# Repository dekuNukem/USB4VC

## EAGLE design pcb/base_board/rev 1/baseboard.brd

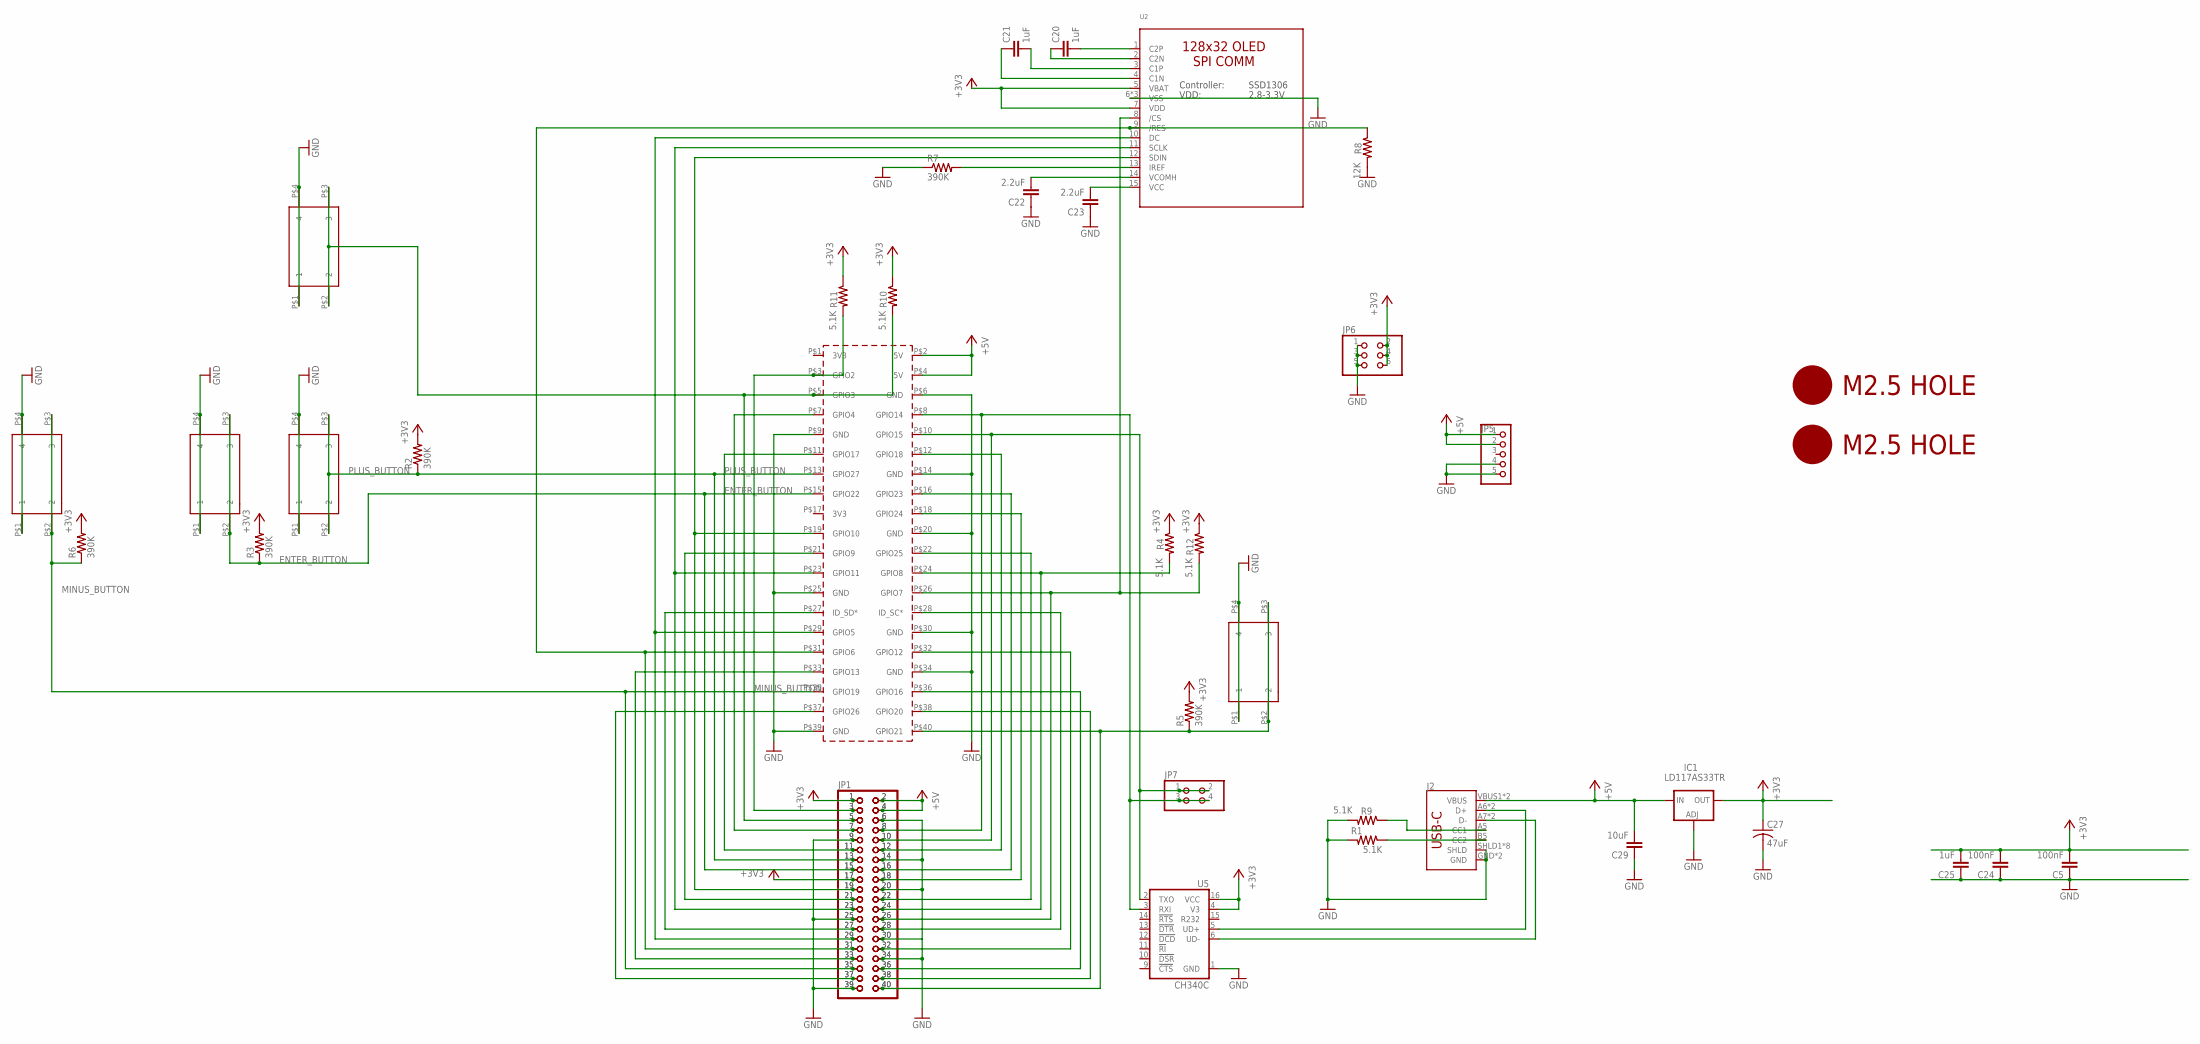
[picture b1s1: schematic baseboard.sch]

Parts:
C5, C24: 100nF; 0805
C20, C21, C25: 1uF; 0805
C22, C23: 2.2uF; 0805
C27: 47uF; C1210
C29: 10uF; 0805
IC1: LD117AS33TR; SOT223
J2: USB_C16PIN; USB-C-16P
JP1, JP2: PINHD-2X20-BIG; 2X20-BIG
JP5: PINHD-1X5; 1X05
JP6: PINHD-2X3; 2X03
JP7: PINHD-2X2; 2X02
PCB1: RPI3NO-CONNECTORS; RPI3-NO-CONNECTORS
R1, R4, R9, R10, R11, R12: 5.1K; 0805
R2, R3, R5, R6, R7: 390K; 0805
R8: 12K; 0805
SW1, SW2, SW3, SW4, SW20: 324_SW; 342_SWICH_FOOT
U2: LUL_DISP_OLED_UG-2864HSWEG01; LUL_UG-2864HSWEG01_1.3_WRAPAROUND
U5: CH340C; SO016
U$2, U$3: M2.5HOLE

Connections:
+3V3: C5.2, C24.2, C25.2, C27.1, IC1.4 (OUT), JP1.1, JP1.17, JP2.1, JP2.17, JP6.2, JP6.4, JP6.6, R2.2, R3.2, R4.1, R5.2, R6.2, R10.1, R11.1, R12.1, U2.5 (VBAT), U2.7 (VDD), U5.4 (V3), U5.16 (VCC); also elsewhere on the board
+5V: C29.2, IC1.3 (IN), J2.VBUS1 (VBUS), J2.VBUS2 (VBUS), JP1.2, JP1.4, JP2.2, JP2.4, JP5.1, JP5.2, JP5.3, PCB1.P$2 (5V), PCB1.P$4 (5V)
ENTER_BUTTON: JP1.15, JP2.15, PCB1.P$15 (GPIO22), R3.1, SW20.P$2 (2), SW20.P$3 (3)
GND: C5.1, C22.1, C23.1, C24.1, C25.1, C27.2, C29.1, IC1.1 (ADJ), J2.GND, J2.GND2 (GND), J2.SHLD1 (SHLD), J2.SHLD2 (SHLD), J2.SHLD3 (SHLD), J2.SHLD4 (SHLD), J2.SHLD5 (SHLD), J2.SHLD6 (SHLD), J2.SHLD7 (SHLD), J2.SHLD8 (SHLD), JP1.6, JP1.9, JP1.14, JP1.20, JP1.25, JP1.30, JP1.34, JP1.39, JP2.6, JP2.9, JP2.14, JP2.20, JP2.25, JP2.30, JP2.34, JP2.39, JP5.4, JP5.5, JP6.1, JP6.3, JP6.5, PCB1.P$6 (GND), PCB1.P$9 (GND), PCB1.P$14 (GND), PCB1.P$20 (GND), PCB1.P$25 (GND), PCB1.P$30 (GND), PCB1.P$34 (GND), PCB1.P$39 (GND), R1.2, R7.1, R8.2, R9.2, SW1.P$1 (1), SW1.P$4 (4), SW2.P$1 (1), SW2.P$4 (4), SW3.P$1 (1), SW3.P$4 (4), SW4.P$1 (1), SW4.P$4 (4), SW20.P$1 (1), SW20.P$4 (4), U2.6 (VSS), U2.16 (VSS), U2.17 (VSS), U5.1 (GND); also elsewhere on the board
MINUS_BUTTON: JP1.35, JP2.35, PCB1.P$35 (GPIO19), R6.1, SW4.P$2 (2), SW4.P$3 (3)
unnamed: J2.A6 (D+), J2.B6 (D+), U5.5 (UD+)
unnamed: J2.A5 (CC1), R9.1
unnamed: J2.A7 (D-), J2.B7 (D-), U5.6 (UD-)
unnamed: JP1.3, JP2.3, PCB1.P$3 (GPIO2), R11.2
unnamed: JP1.5, JP2.5, PCB1.P$5 (GPIO3), R10.2, SW2.P$2 (2), SW2.P$3 (3)
unnamed: J2.B5 (CC2), R1.1
unnamed: JP1.7, JP2.7, PCB1.P$7 (GPIO4)
unnamed: JP1.11, JP2.11, PCB1.P$11 (GPIO17)
unnamed: JP1.19, JP2.19, PCB1.P$19 (GPIO10), U2.12 (SDIN)
unnamed: JP1.21, JP2.21, PCB1.P$21 (GPIO9)
unnamed: JP1.23, JP2.23, PCB1.P$23 (GPIO11), U2.11 (SCLK)
unnamed: JP1.27, JP2.27, PCB1.P$27 (ID_SD*)
unnamed: JP1.29, JP2.29, PCB1.P$29 (GPIO5), U2.10 (DC)
unnamed: JP1.33, JP2.33, PCB1.P$33 (GPIO13)
unnamed: JP1.37, JP2.37, PCB1.P$37 (GPIO26)
unnamed: JP1.12, JP2.12, PCB1.P$12 (GPIO18)
unnamed: JP1.16, JP2.16, PCB1.P$16 (GPIO23)
unnamed: JP1.18, JP2.18, PCB1.P$18 (GPIO24)
unnamed: JP1.22, JP2.22, PCB1.P$22 (GPIO25)
unnamed: JP1.24, JP2.24, PCB1.P$24 (GPIO8), R4.2
unnamed: JP1.26, JP2.26, PCB1.P$26 (GPIO7), R12.2, U2.8 (/CS)
unnamed: JP1.28, JP2.28, PCB1.P$28 (ID_SC*)
unnamed: JP1.32, JP2.32, PCB1.P$32 (GPIO12)
unnamed: JP1.36, JP2.36, PCB1.P$36 (GPIO16)
unnamed: JP1.38, JP2.38, PCB1.P$38 (GPIO20)
unnamed: JP1.40, JP2.40, PCB1.P$40 (GPIO21), R5.1, SW3.P$2 (2), SW3.P$3 (3)
unnamed: C20.2, U2.1 (C2P)
unnamed: C20.1, U2.2 (C2N)
unnamed: C21.2, U2.3 (C1P)
unnamed: C21.1, U2.4 (C1N)
unnamed: R7.2, U2.13 (IREF)
unnamed: C22.2, U2.14 (VCOMH)
unnamed: C23.2, U2.15 (VCC)
unnamed: JP1.31, JP2.31, PCB1.P$31 (GPIO6), R8.1, U2.9 (/RES)
PLUS_BUTTON: JP1.13, JP2.13, PCB1.P$13 (GPIO27), R2.1, SW1.P$2 (2), SW1.P$3 (3)
RPI_RX: JP1.10, JP2.10, JP7.1, JP7.2, PCB1.P$10 (GPIO15), U5.2 (TXO)
RPI_TX: JP1.8, JP2.8, JP7.3, JP7.4, PCB1.P$8 (GPIO14), U5.3 (RXI)

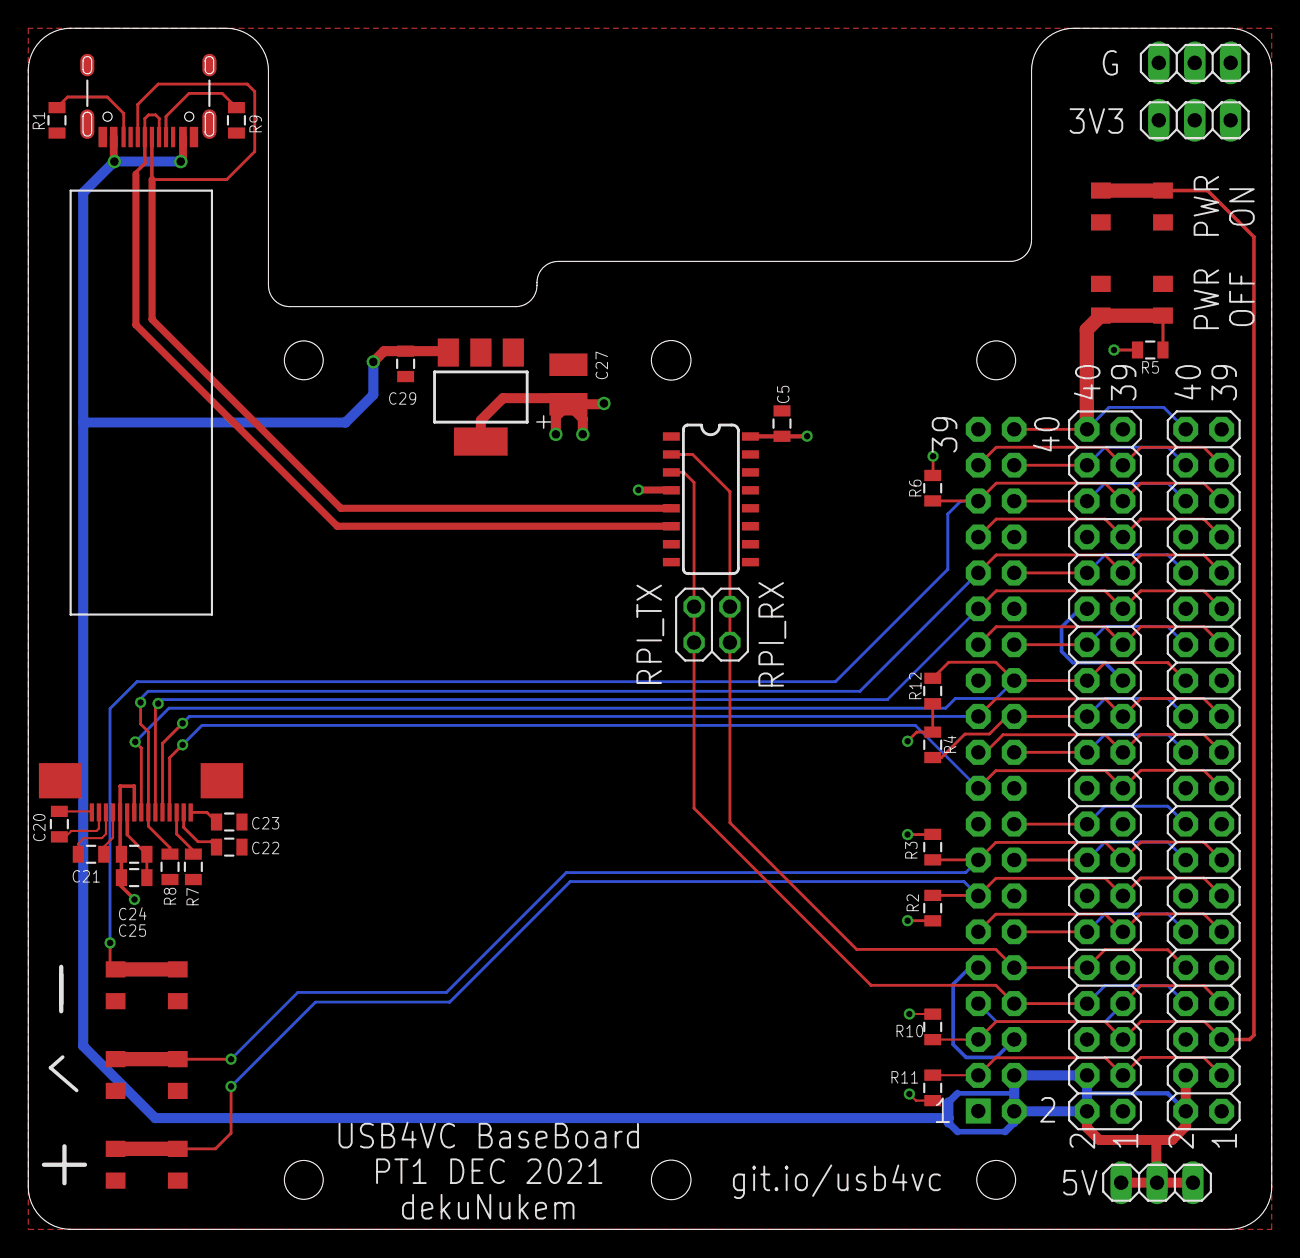
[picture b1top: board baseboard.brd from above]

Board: 2 copper layers, 88.0 x 85.0 mm, 39 parts (0 on the bottom side), 42 nets.

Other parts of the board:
JP3, JP4: 1X03

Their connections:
+3V3: JP3.1, JP3.2, JP3.3; also elsewhere on the board
GND: JP4.1, JP4.2, JP4.3; also elsewhere on the board

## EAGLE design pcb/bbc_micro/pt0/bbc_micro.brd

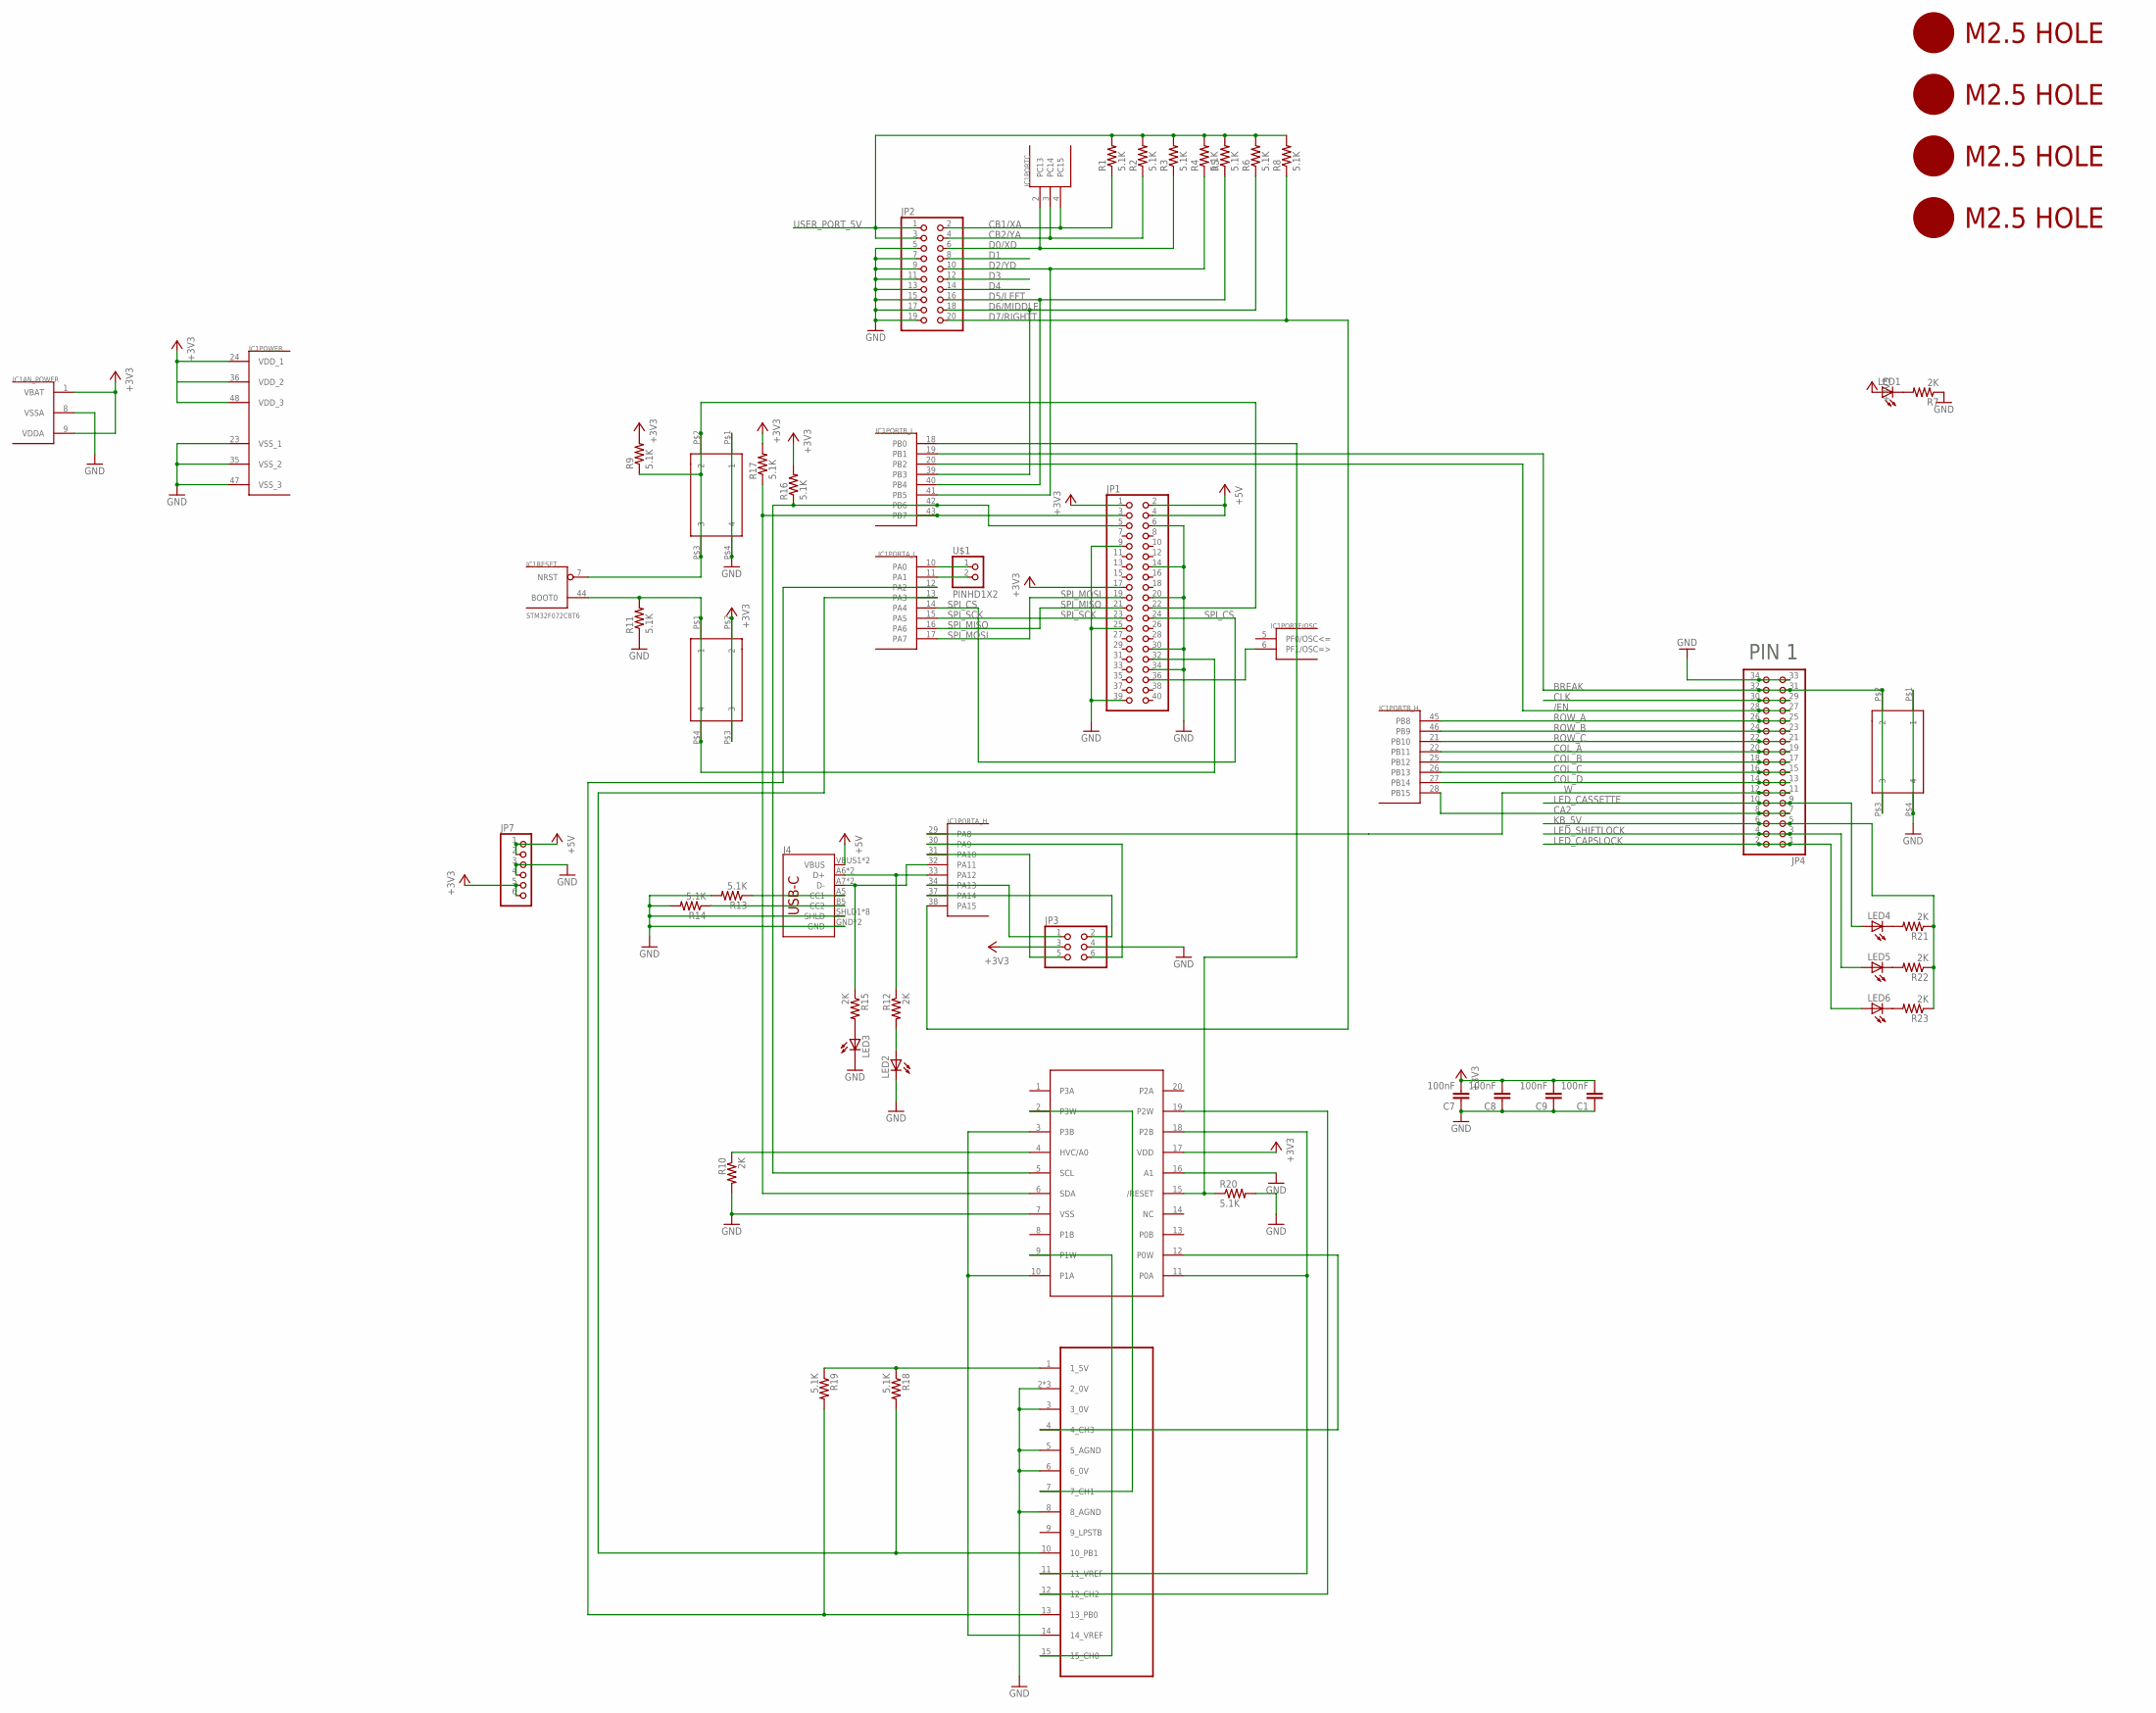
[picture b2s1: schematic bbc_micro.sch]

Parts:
C1, C7, C8, C9: 100nF; 0805@1
IC1: STM32F072C8T6; TQFP48
J4: USB_C16PIN; USB-C-16P
JP1: PINHD-2X20-BIG; 2X20-BIG
JP2: PINHD-2X10/90; 2X10/90
JP3: PINHD-2X3; 2X03
JP4: PINHD-2X17/90; 2X17/90
JP7: PINHD-1X6CB; 1X06-CLEANBIG
LED1, LED2, LED3, LED4, LED5, LED6: LEDCHIP-LED0805; CHIP-LED0805
R1, R2, R3, R4, R5, R6, R8, R9, R11, R13, R14, R16, R17, R18, R19, R20: 5.1K; 0805
R7, R10, R12, R15, R21, R22, R23: 2K; 0805
SW1, SW2, SW3: 324_SW; 342_SWICH_FOOT
U$1: PINHD1X2; 1X02
U$2, U$3, U$6, U$7: M2.5HOLE
U$5: MCP4451; TSSOP20
U$9: BBC_15P; DA15

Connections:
+3V3: C1.2, C7.2, C8.2, C9.2, IC1.1 (VBAT), IC1.9 (VDDA), IC1.24 (VDD_1), IC1.36 (VDD_2), IC1.48 (VDD_3), JP1.1, JP1.17, JP3.3, JP7.5, JP7.6, LED1.A, R9.2, R16.2, R17.2, SW2.P$2 (2), SW2.P$3 (3), U$5.17 (VDD)
+5V: J4.VBUS1 (VBUS), J4.VBUS2 (VBUS), JP1.2, JP1.4, JP7.1, JP7.2
/EN: IC1.20 (PB2), JP4.27, JP4.28
BREAK: IC1.19 (PB1), JP4.31, JP4.32, SW3.P$2 (2), SW3.P$3 (3)
CA2: IC1.28 (PB15), JP4.7, JP4.8
CB1/XA: IC1.4 (PC15), JP2.2, R1.1
CB2/YA: IC1.3 (PC14), JP2.4, R2.1
CLK: JP4.29, JP4.30
COL_A: IC1.22 (PB11), JP4.19, JP4.20
COL_B: IC1.25 (PB12), JP4.17, JP4.18
COL_C: IC1.26 (PB13), JP4.15, JP4.16
COL_D: IC1.27 (PB14), JP4.13, JP4.14
D0/XD: IC1.2 (PC13), JP2.6, R3.1
D1: JP2.8
D2/YD: IC1.41 (PB5), JP2.10, R4.1
D3: JP2.12
D4: JP2.14
D5/LEFT: IC1.40 (PB4), JP2.16, R5.1
D6/MIDDLE: IC1.39 (PB3), JP2.18, R6.1
D7/RIGHTT: IC1.38 (PA15), JP2.20, R8.1
GND: C1.1, C7.1, C8.1, C9.1, IC1.8 (VSSA), IC1.23 (VSS_1), IC1.35 (VSS_2), IC1.47 (VSS_3), J4.GND, J4.GND2 (GND), J4.SHLD1 (SHLD), J4.SHLD2 (SHLD), J4.SHLD3 (SHLD), J4.SHLD4 (SHLD), J4.SHLD5 (SHLD), J4.SHLD6 (SHLD), J4.SHLD7 (SHLD), J4.SHLD8 (SHLD), JP1.6, JP1.9, JP1.14, JP1.20, JP1.25, JP1.30, JP1.34, JP1.39, JP2.5, JP2.7, JP2.9, JP2.11, JP2.13, JP2.15, JP2.17, JP2.19, JP3.4, JP4.33, JP4.34, JP7.3, JP7.4, LED2.C, LED3.C, R7.1, R10.2, R11.1, R13.2, R14.2, R20.2, SW1.P$1 (1), SW1.P$4 (4), SW3.P$1 (1), SW3.P$4 (4), U$5.7 (VSS), U$5.16 (A1), U$9.2 (2_0V), U$9.3 (3_0V), U$9.5 (5_AGND), U$9.6 (6_0V), U$9.8 (8_AGND), U$9.G1 (2_0V), U$9.G2 (2_0V)
KB_5V: JP4.5, JP4.6, R21.1, R22.1, R23.1
LED_CAPSLOCK: JP4.1, JP4.2, LED6.A
LED_CASSETTE: JP4.9, JP4.10, LED4.A
LED_SHIFTLOCK: JP4.3, JP4.4, LED5.A
unnamed: J4.A5 (CC1), R13.1
unnamed: LED2.A, R12.2
unnamed: LED4.C, R21.2
unnamed: R10.1, U$5.4 (HVC/A0)
unnamed: U$5.2 (P3W), U$9.7 (7_CH1)
unnamed: U$5.9 (P1W), U$9.15 (15_CH0)
unnamed: J4.B5 (CC2), R14.1
unnamed: IC1.33 (PA12), J4.A6 (D+), J4.B6 (D+), R12.1
unnamed: IC1.32 (PA11), J4.A7 (D-), J4.B7 (D-), R15.1
unnamed: U$5.19 (P2W), U$9.12 (12_CH2)
unnamed: U$5.12 (P0W), U$9.4 (4_CH3)
unnamed: IC1.31 (PA10), JP3.5
unnamed: IC1.7 (NRST), JP1.22, R9.1, SW1.P$2 (2), SW1.P$3 (3)
unnamed: IC1.30 (PA9), JP3.6
unnamed: IC1.34 (PA13), JP3.1
unnamed: IC1.37 (PA14), JP3.2
unnamed: U$5.3 (P3B), U$5.10 (P1A), U$9.14 (14_VREF)
unnamed: IC1.44 (BOOT0), JP1.32, R11.2, SW2.P$1 (1), SW2.P$4 (4)
unnamed: U$5.11 (P0A), U$5.18 (P2B), U$9.11 (11_VREF)
unnamed: R18.1, R19.1, U$9.1 (1_5V)
unnamed: IC1.13 (PA3), R18.2, U$9.10 (10_PB1)
unnamed: IC1.42 (PB6), JP1.5, R16.1, U$5.5 (SCL)
unnamed: IC1.43 (PB7), JP1.3, R17.1, U$5.6 (SDA)
unnamed: IC1.10 (PA0), U$1.1
unnamed: IC1.18 (PB0), R20.1, U$5.15 (/RESET)
unnamed: LED5.C, R22.2
unnamed: LED6.C, R23.2
unnamed: LED3.A, R15.2
unnamed: LED1.C, R7.2
unnamed: IC1.12 (PA2), R19.2, U$9.13 (13_PB0)
unnamed: IC1.11 (PA1), U$1.2
unnamed: IC1.6 (PF1/OSC=>), JP1.36
ROW_A: IC1.45 (PB8), JP4.25, JP4.26
ROW_B: IC1.46 (PB9), JP4.23, JP4.24
ROW_C: IC1.21 (PB10), JP4.21, JP4.22
SPI_CS: IC1.14 (PA4), JP1.24
SPI_MISO: IC1.16 (PA6), JP1.21
SPI_MOSI: IC1.17 (PA7), JP1.19
SPI_SCK: IC1.15 (PA5), JP1.23
USER_PORT_5V: JP2.1, JP2.3, R1.2, R2.2, R3.2, R4.2, R5.2, R6.2, R8.2
W: IC1.29 (PA8), JP4.11, JP4.12

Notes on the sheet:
PIN 1

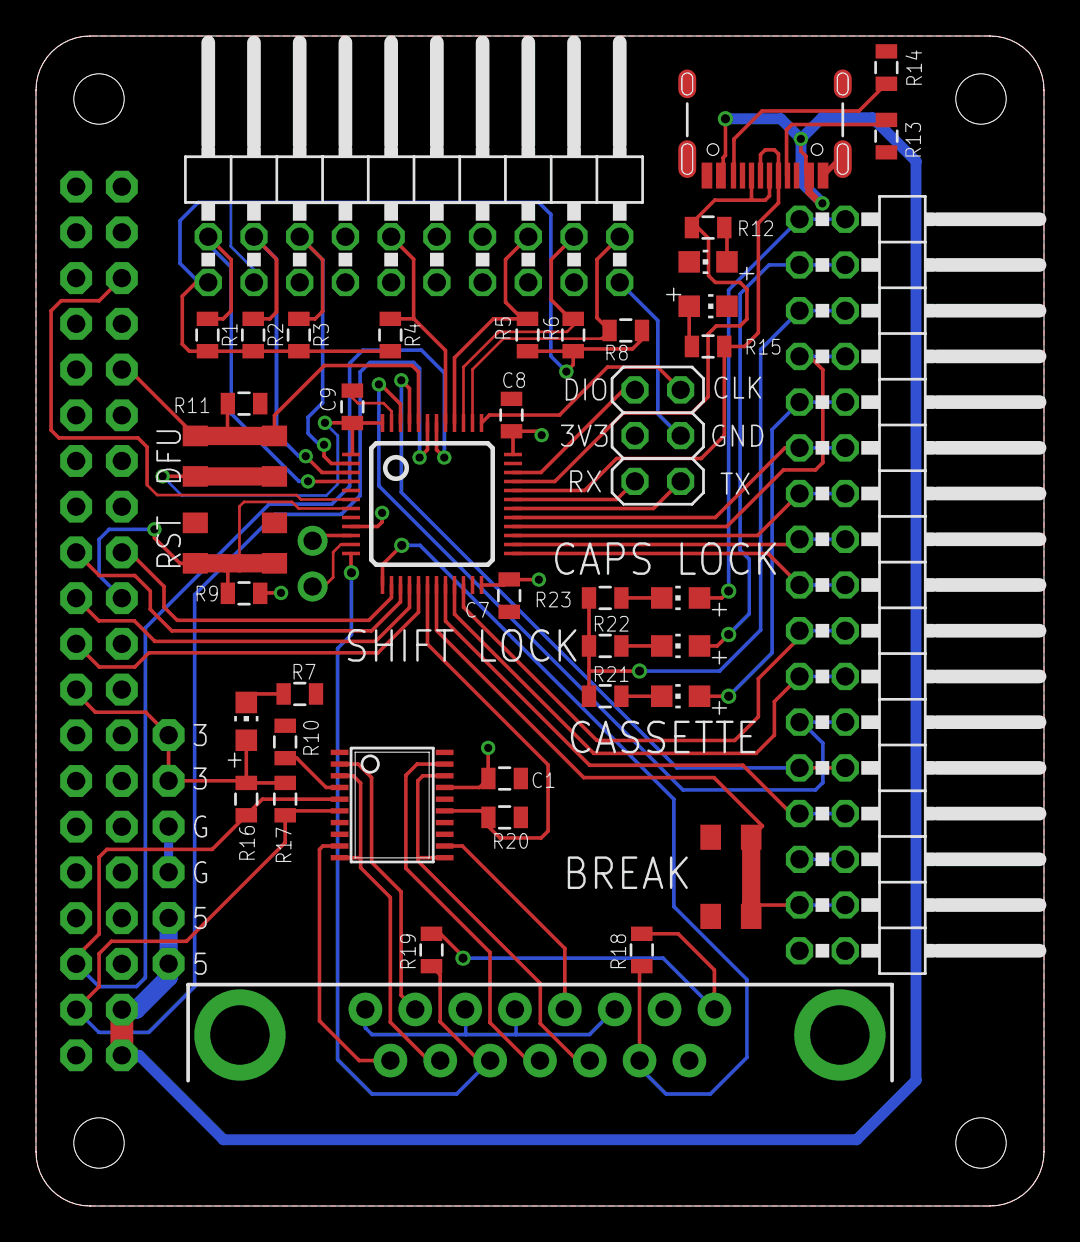
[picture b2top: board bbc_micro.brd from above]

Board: 2 copper layers, 56.0 x 65.0 mm, 50 parts (1 on the bottom side), 63 nets.

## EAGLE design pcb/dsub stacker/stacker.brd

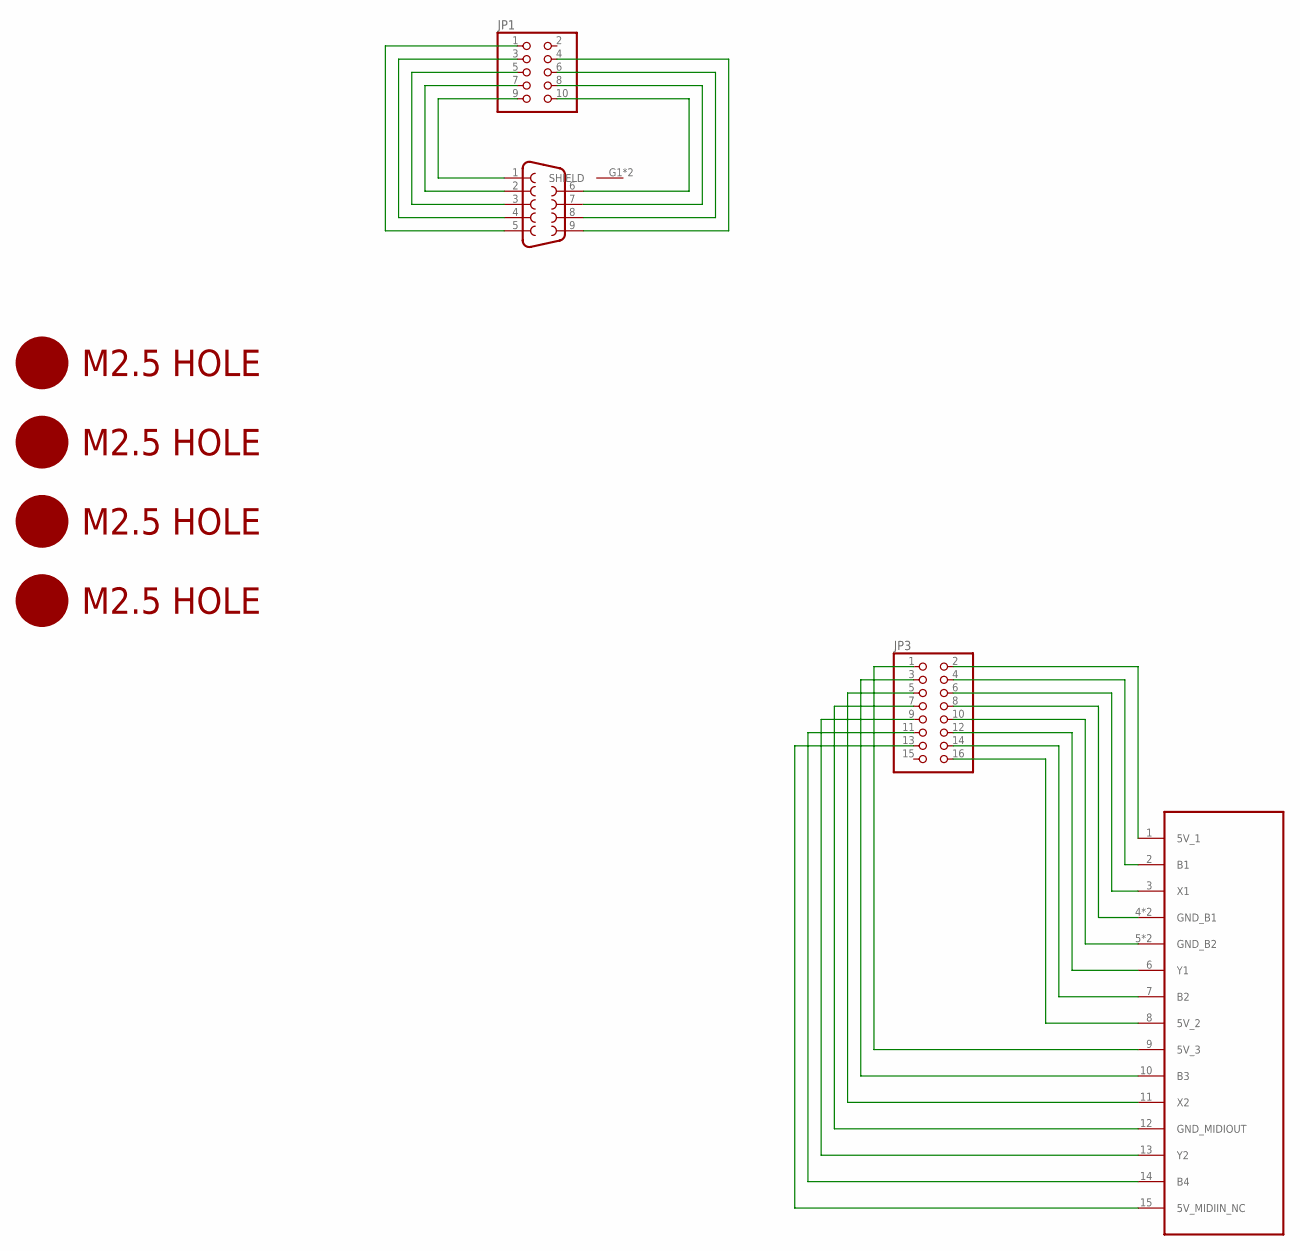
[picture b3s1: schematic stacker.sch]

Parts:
J5: DB9MALE; DB9_MALE
JP1: PINHD-2X5; 2X05
JP3: PINHD-2X8; 2X08
U$2, U$3, U$4, U$5: M2.5HOLE
U$11: GAMEPORT_15P; DA15

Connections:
unnamed: J5.1, JP1.9
unnamed: J5.2, JP1.7
unnamed: J5.3, JP1.5
unnamed: J5.4, JP1.3
unnamed: J5.5, JP1.1
unnamed: J5.6, JP1.10
unnamed: J5.7, JP1.8
unnamed: J5.8, JP1.6
unnamed: J5.9, JP1.4
unnamed: JP3.2, U$11.1 (5V_1)
unnamed: JP3.4, U$11.2 (B1)
unnamed: JP3.6, U$11.3 (X1)
unnamed: JP3.8, U$11.4 (GND_B1), U$11.G1 (GND_B1)
unnamed: JP3.10, U$11.5 (GND_B2), U$11.G2 (GND_B2)
unnamed: JP3.12, U$11.6 (Y1)
unnamed: JP3.14, U$11.7 (B2)
unnamed: JP3.16, U$11.8 (5V_2)
unnamed: JP3.1, U$11.9 (5V_3)
unnamed: JP3.3, U$11.10 (B3)
unnamed: JP3.5, U$11.11 (X2)
unnamed: JP3.7, U$11.12 (GND_MIDIOUT)
unnamed: JP3.9, U$11.13 (Y2)
unnamed: JP3.11, U$11.14 (B4)
unnamed: JP3.13, U$11.15 (5V_MIDIIN_NC)

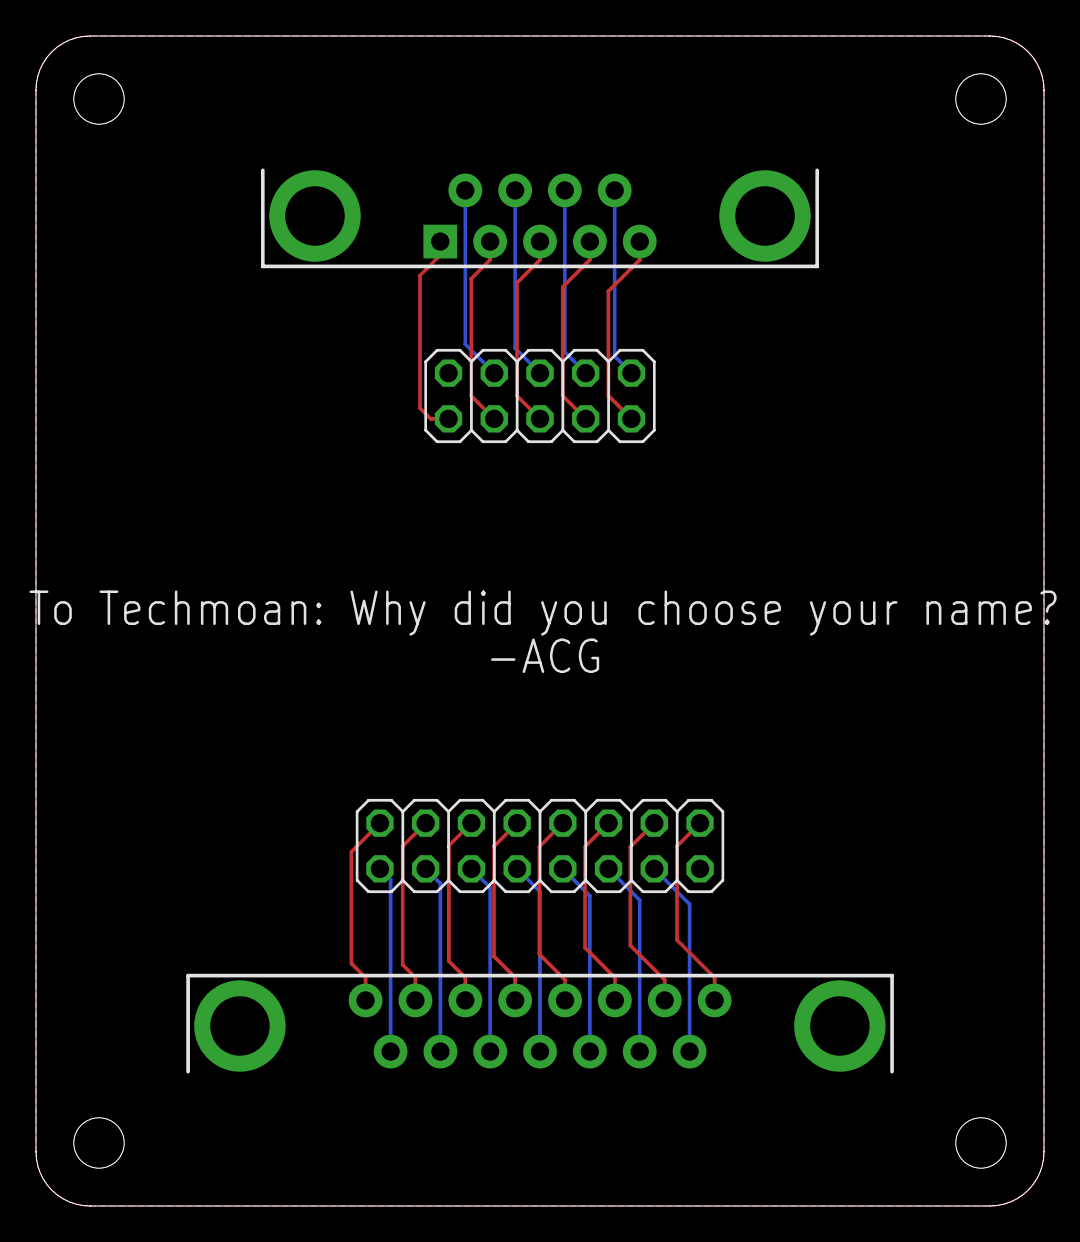
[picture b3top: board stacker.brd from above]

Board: 2 copper layers, 56.0 x 65.0 mm, 8 parts (0 on the bottom side), 24 nets.

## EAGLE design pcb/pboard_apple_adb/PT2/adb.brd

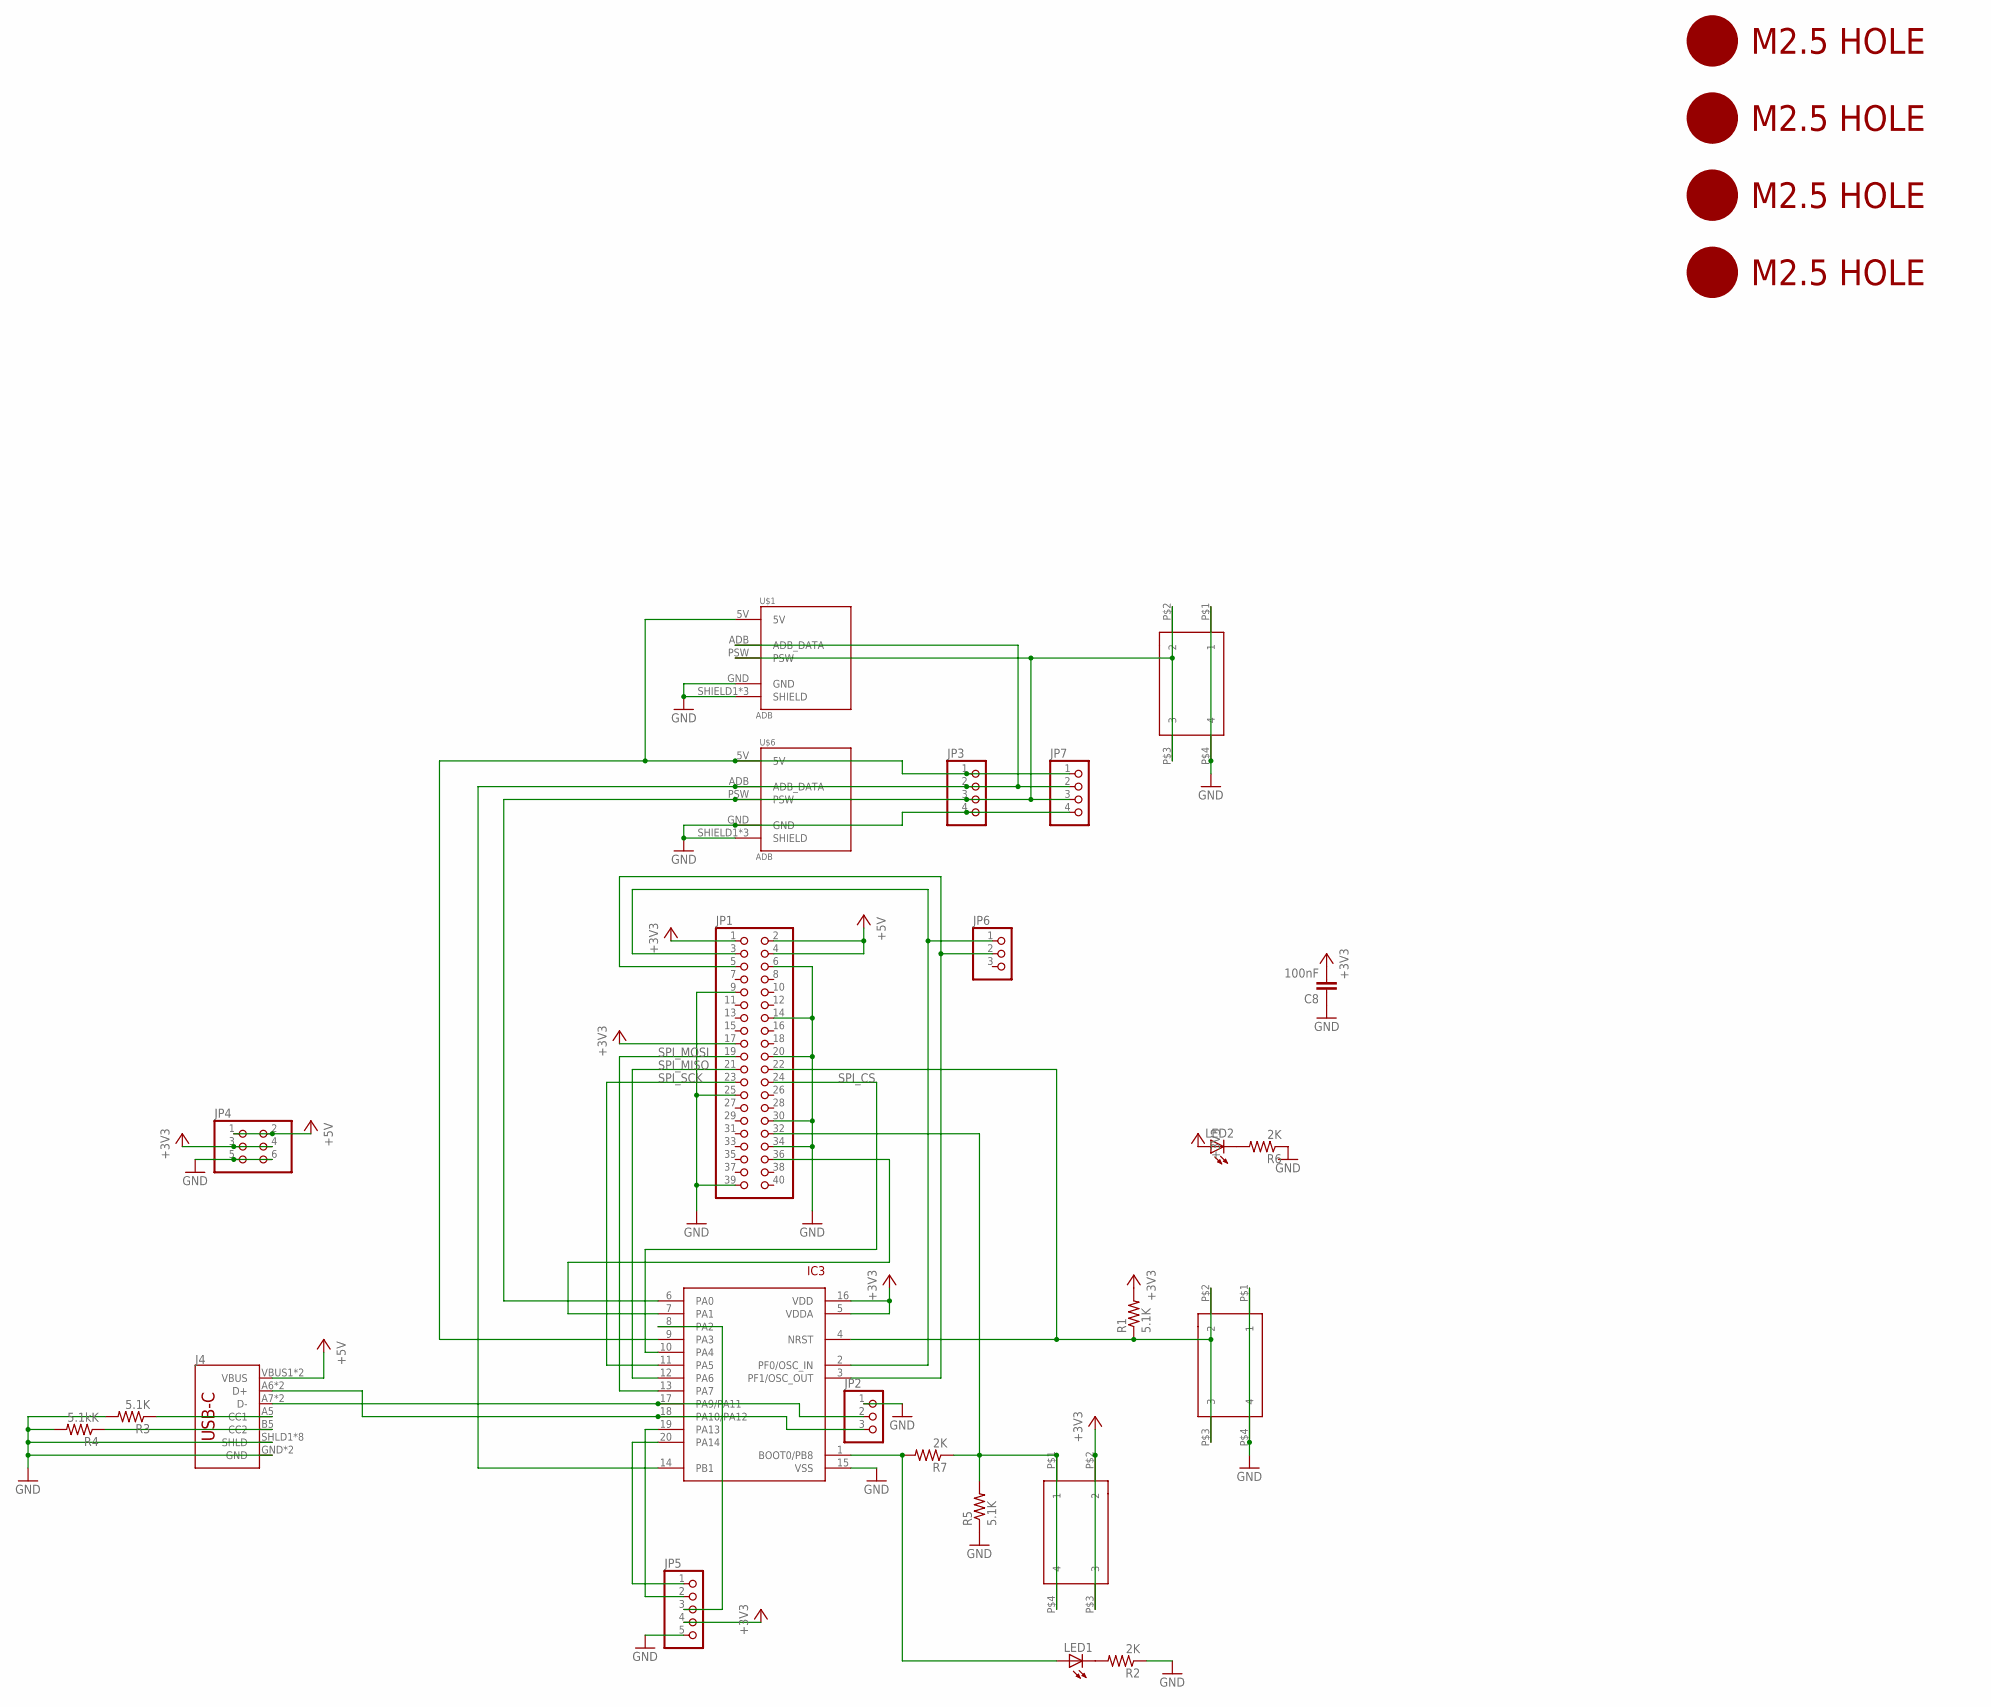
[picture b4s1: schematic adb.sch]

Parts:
C8: 100nF; 0805@1
IC3: STM32F042F4; TSSOP20
J4: USB_C16PIN; USB-C-16P
JP1: PINHD-2X20-BIG; 2X20-BIG
JP2, JP6: PINHD-1X3; 1X03
JP3, JP7: PINHD-1X4; 1X04
JP4: PINHD-2X3; 2X03
JP5: PINHD-1X5; 1X05
LED1, LED2: LEDCHIP-LED0805; CHIP-LED0805
R1, R3, R5: 5.1K; 0805
R2, R6, R7: 2K; 0805
R4: 5.1kK; 0805
SW1, SW2, SW4: 324_SW; 342_SWICH_FOOT
U$1, U$6: ADB; DIN4
U$2, U$3, U$4, U$5: M2.5HOLE

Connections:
+3V3: C8.2, IC3.5 (VDDA), IC3.16 (VDD), JP1.1, JP1.17, JP4.3, JP4.4, JP5.4, LED2.A, R1.2, SW1.P$2 (2), SW1.P$3 (3)
+5V: J4.VBUS1 (VBUS), J4.VBUS2 (VBUS), JP1.2, JP1.4, JP4.1, JP4.2
GND: C8.1, IC3.15 (VSS), J4.GND, J4.GND2 (GND), J4.SHLD1 (SHLD), J4.SHLD2 (SHLD), J4.SHLD3 (SHLD), J4.SHLD4 (SHLD), J4.SHLD5 (SHLD), J4.SHLD6 (SHLD), J4.SHLD7 (SHLD), J4.SHLD8 (SHLD), JP1.6, JP1.9, JP1.14, JP1.20, JP1.25, JP1.30, JP1.34, JP1.39, JP2.1, JP3.4, JP4.5, JP4.6, JP5.5, JP7.4, R2.1, R3.2, R4.2, R5.1, R6.1, SW2.P$1 (1), SW2.P$4 (4), SW4.P$1 (1), SW4.P$4 (4), U$1.GND, U$1.SHIELD1 (SHIELD), U$1.SHIELD2 (SHIELD), U$1.SHIELD3 (SHIELD), U$6.GND, U$6.SHIELD1 (SHIELD), U$6.SHIELD2 (SHIELD), U$6.SHIELD3 (SHIELD)
unnamed: J4.A5 (CC1), R3.1
unnamed: JP1.32, R5.2, R7.1, SW1.P$1 (1), SW1.P$4 (4)
unnamed: IC3.18 (PA10/PA12), J4.A6 (D+), J4.B6 (D+), JP2.3
unnamed: IC3.17 (PA9/PA11), J4.A7 (D-), J4.B7 (D-), JP2.2
unnamed: IC3.8 (PA2), JP5.3
unnamed: IC3.19 (PA13), JP5.2
unnamed: J4.B5 (CC2), R4.1
unnamed: IC3.20 (PA14), JP5.1
unnamed: IC3.1 (BOOT0/PB8), LED1.A, R7.2
unnamed: IC3.2 (PF0/OSC_IN), JP1.3, JP6.1
unnamed: IC3.3 (PF1/OSC_OUT), JP1.5, JP6.2
unnamed: IC3.7 (PA1), JP1.36
unnamed: IC3.4 (NRST), JP1.22, R1.1, SW4.P$2 (2), SW4.P$3 (3)
unnamed: IC3.9 (PA3), JP3.1, JP7.1, U$1.5V, U$6.5V
unnamed: IC3.14 (PB1), JP3.2, JP7.2, U$1.ADB (ADB_DATA), U$6.ADB (ADB_DATA)
unnamed: LED1.C, R2.2
unnamed: IC3.6 (PA0), JP3.3, JP7.3, SW2.P$2 (2), SW2.P$3 (3), U$1.PSW, U$6.PSW
unnamed: LED2.C, R6.2
SPI_CS: IC3.10 (PA4), JP1.24
SPI_MISO: IC3.12 (PA6), JP1.21
SPI_MOSI: IC3.13 (PA7), JP1.19
SPI_SCK: IC3.11 (PA5), JP1.23

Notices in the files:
parts and their libraries:
SparkFun-Connectors: Licensing: Creative Commons ShareAlike 4.0 International - https://creativecommons.org/licenses/by-sa/4.0
SparkFun-Aesthetics: Licensing: CC v3.0 Share-Alike You are welcome to use this library for commercial purposes.
